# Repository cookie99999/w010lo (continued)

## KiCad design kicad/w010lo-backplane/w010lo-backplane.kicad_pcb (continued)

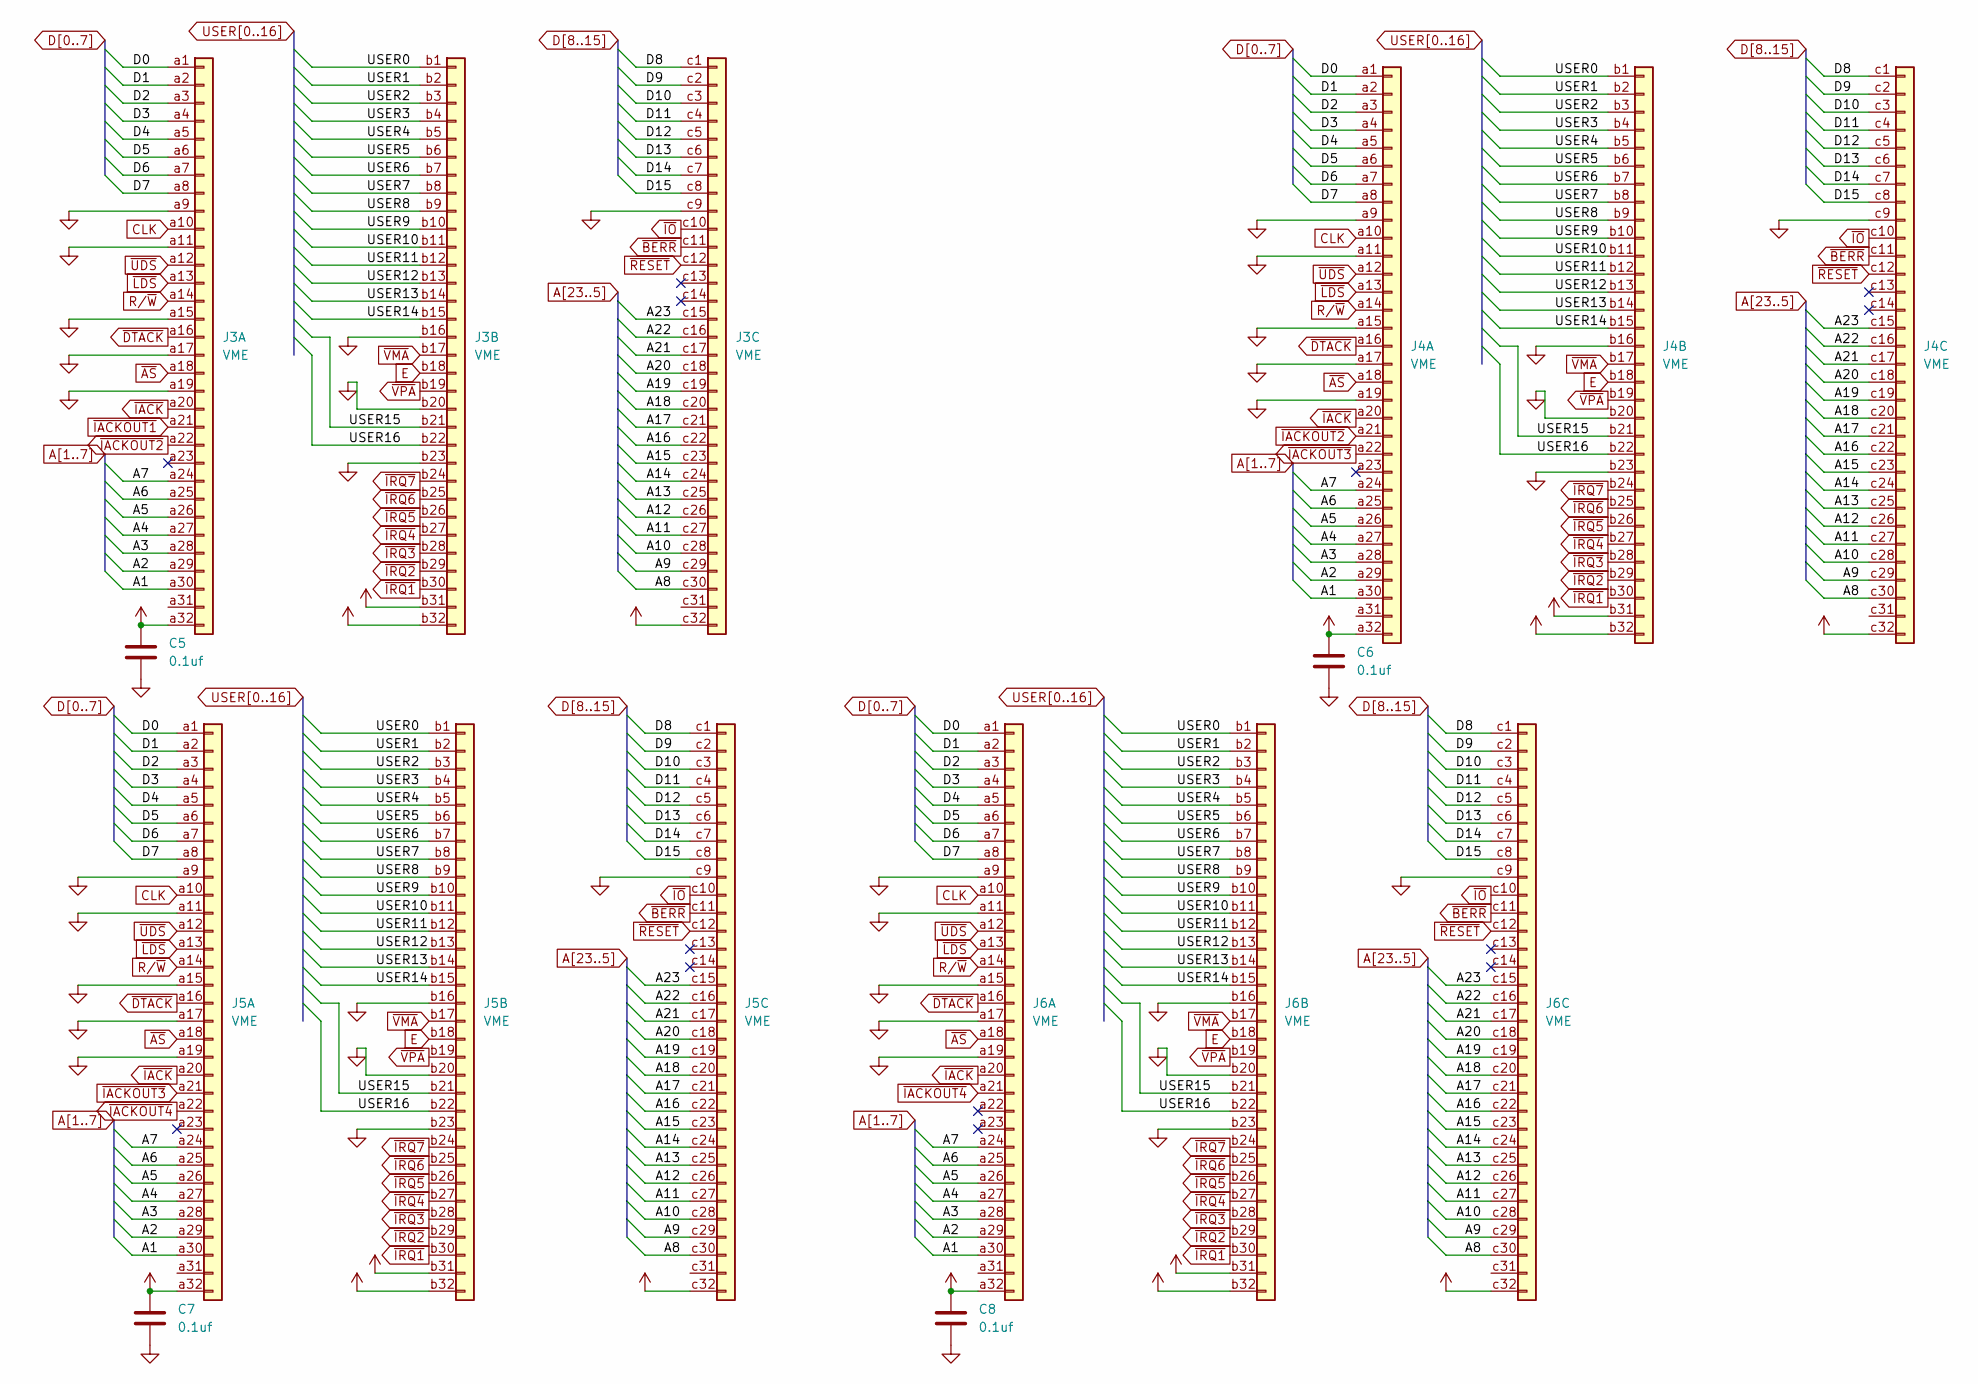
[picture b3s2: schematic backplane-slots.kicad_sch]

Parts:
C5, C6, C7, C8: 0.1uf; C_Disc_D5.0mm_W2.5mm_P5.00mm
J3, J4, J5, J6: VME; DIN41612_C_3x32_Female_Vertical_THT

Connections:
A1: J3.a30, J4.a30, J5.a30, J6.a30; also elsewhere on the board
A2: J3.a29, J4.a29, J5.a29, J6.a29; also elsewhere on the board
A3: J3.a28, J4.a28, J5.a28, J6.a28; also elsewhere on the board
A4: J3.a27, J4.a27, J5.a27, J6.a27; also elsewhere on the board
A5: J3.a26, J4.a26, J5.a26, J6.a26; also elsewhere on the board
A6: J3.a25, J4.a25, J5.a25, J6.a25; also elsewhere on the board
A7: J3.a24, J4.a24, J5.a24, J6.a24; also elsewhere on the board
A8: J3.c30, J4.c30, J5.c30, J6.c30; also elsewhere on the board
A9: J3.c29, J4.c29, J5.c29, J6.c29; also elsewhere on the board
A10: J3.c28, J4.c28, J5.c28, J6.c28; also elsewhere on the board
A11: J3.c27, J4.c27, J5.c27, J6.c27; also elsewhere on the board
A12: J3.c26, J4.c26, J5.c26, J6.c26; also elsewhere on the board
A13: J3.c25, J4.c25, J5.c25, J6.c25; also elsewhere on the board
A14: J3.c24, J4.c24, J5.c24, J6.c24; also elsewhere on the board
A15: J3.c23, J4.c23, J5.c23, J6.c23; also elsewhere on the board
A16: J3.c22, J4.c22, J5.c22, J6.c22; also elsewhere on the board
A17: J3.c21, J4.c21, J5.c21, J6.c21; also elsewhere on the board
A18: J3.c20, J4.c20, J5.c20, J6.c20; also elsewhere on the board
A19: J3.c19, J4.c19, J5.c19, J6.c19; also elsewhere on the board
A20: J3.c18, J4.c18, J5.c18, J6.c18; also elsewhere on the board
A21: J3.c17, J4.c17, J5.c17, J6.c17; also elsewhere on the board
A22: J3.c16, J4.c16, J5.c16, J6.c16; also elsewhere on the board
A23: J3.c15, J4.c15, J5.c15, J6.c15; also elsewhere on the board
CLK: J3.a10, J4.a10, J5.a10, J6.a10; also elsewhere on the board
D0: J3.a1, J4.a1, J5.a1, J6.a1; also elsewhere on the board
D1: J3.a2, J4.a2, J5.a2, J6.a2; also elsewhere on the board
D2: J3.a3, J4.a3, J5.a3, J6.a3; also elsewhere on the board
D3: J3.a4, J4.a4, J5.a4, J6.a4; also elsewhere on the board
D4: J3.a5, J4.a5, J5.a5, J6.a5; also elsewhere on the board
D5: J3.a6, J4.a6, J5.a6, J6.a6; also elsewhere on the board
D6: J3.a7, J4.a7, J5.a7, J6.a7; also elsewhere on the board
D7: J3.a8, J4.a8, J5.a8, J6.a8; also elsewhere on the board
D8: J3.c1, J4.c1, J5.c1, J6.c1; also elsewhere on the board
D9: J3.c2, J4.c2, J5.c2, J6.c2; also elsewhere on the board
D10: J3.c3, J4.c3, J5.c3, J6.c3; also elsewhere on the board
D11: J3.c4, J4.c4, J5.c4, J6.c4; also elsewhere on the board
D12: J3.c5, J4.c5, J5.c5, J6.c5; also elsewhere on the board
D13: J3.c6, J4.c6, J5.c6, J6.c6; also elsewhere on the board
D14: J3.c7, J4.c7, J5.c7, J6.c7; also elsewhere on the board
D15: J3.c8, J4.c8, J5.c8, J6.c8; also elsewhere on the board
E: J3.b18, J4.b18, J5.b18, J6.b18; also elsewhere on the board
GND: C5.2, C6.2, C7.2, C8.2, J3.a9, J3.a11, J3.a15, J3.a17, J3.a19, J3.b16, J3.b20, J3.b23, J3.c9, J4.a9, J4.a11, J4.a15, J4.a17, J4.a19, J4.b16, J4.b20, J4.b23, J4.c9, J5.a9, J5.a11, J5.a15, J5.a17, J5.a19, J5.b16, J5.b20, J5.b23, J5.c9, J6.a9, J6.a11, J6.a15, J6.a17, J6.a19, J6.b16, J6.b20, J6.b23, J6.c9; also elsewhere on the board
R/~W: J3.a14, J4.a14, J5.a14, J6.a14; also elsewhere on the board
USER0: J3.b1, J4.b1, J5.b1, J6.b1; also elsewhere on the board
USER1: J3.b2, J4.b2, J5.b2, J6.b2; also elsewhere on the board
USER2: J3.b3, J4.b3, J5.b3, J6.b3; also elsewhere on the board
USER3: J3.b4, J4.b4, J5.b4, J6.b4; also elsewhere on the board
USER4: J3.b5, J4.b5, J5.b5, J6.b5; also elsewhere on the board
USER5: J3.b6, J4.b6, J5.b6, J6.b6; also elsewhere on the board
USER6: J3.b7, J4.b7, J5.b7, J6.b7; also elsewhere on the board
USER7: J3.b8, J4.b8, J5.b8, J6.b8; also elsewhere on the board
USER8: J3.b9, J4.b9, J5.b9, J6.b9; also elsewhere on the board
USER9: J3.b10, J4.b10, J5.b10, J6.b10; also elsewhere on the board
USER10: J3.b11, J4.b11, J5.b11, J6.b11; also elsewhere on the board
USER11: J3.b12, J4.b12, J5.b12, J6.b12; also elsewhere on the board
USER12: J3.b13, J4.b13, J5.b13, J6.b13; also elsewhere on the board
USER13: J3.b14, J4.b14, J5.b14, J6.b14; also elsewhere on the board
USER14: J3.b15, J4.b15, J5.b15, J6.b15; also elsewhere on the board
USER15: J3.b21, J4.b21, J5.b21, J6.b21; also elsewhere on the board
USER16: J3.b22, J4.b22, J5.b22, J6.b22; also elsewhere on the board
VCC: C5.1, C6.1, C7.1, C8.1, J3.a32, J3.b31, J3.b32, J3.c32, J4.a32, J4.b31, J4.b32, J4.c32, J5.a32, J5.b31, J5.b32, J5.c32, J6.a32, J6.b31, J6.b32, J6.c32; also elsewhere on the board
~AS: J3.a18, J4.a18, J5.a18, J6.a18; also elsewhere on the board
~BERR: J3.c11, J4.c11, J5.c11, J6.c11; also elsewhere on the board
~DTACK: J3.a16, J4.a16, J5.a16, J6.a16; also elsewhere on the board
~IACKOUT1: J3.a21; also elsewhere on the board
~IACKOUT2: J3.a22, J4.a21
~IACKOUT3: J4.a22, J5.a21
~IACKOUT4: J5.a22, J6.a21
~IACK: J3.a20, J4.a20, J5.a20, J6.a20; also elsewhere on the board
~IO: J3.c10, J4.c10, J5.c10, J6.c10; also elsewhere on the board
~IRQ1: J3.b30, J4.b30, J5.b30, J6.b30; also elsewhere on the board
~IRQ2: J3.b29, J4.b29, J5.b29, J6.b29; also elsewhere on the board
~IRQ3: J3.b28, J4.b28, J5.b28, J6.b28; also elsewhere on the board
~IRQ4: J3.b27, J4.b27, J5.b27, J6.b27; also elsewhere on the board
~IRQ5: J3.b26, J4.b26, J5.b26, J6.b26; also elsewhere on the board
~IRQ6: J3.b25, J4.b25, J5.b25, J6.b25; also elsewhere on the board
~IRQ7: J3.b24, J4.b24, J5.b24, J6.b24; also elsewhere on the board
~LDS: J3.a13, J4.a13, J5.a13, J6.a13; also elsewhere on the board
~RESET: J3.c12, J4.c12, J5.c12, J6.c12; also elsewhere on the board
~UDS: J3.a12, J4.a12, J5.a12, J6.a12; also elsewhere on the board
~VMA: J3.b17, J4.b17, J5.b17, J6.b17; also elsewhere on the board
~VPA: J3.b19, J4.b19, J5.b19, J6.b19; also elsewhere on the board

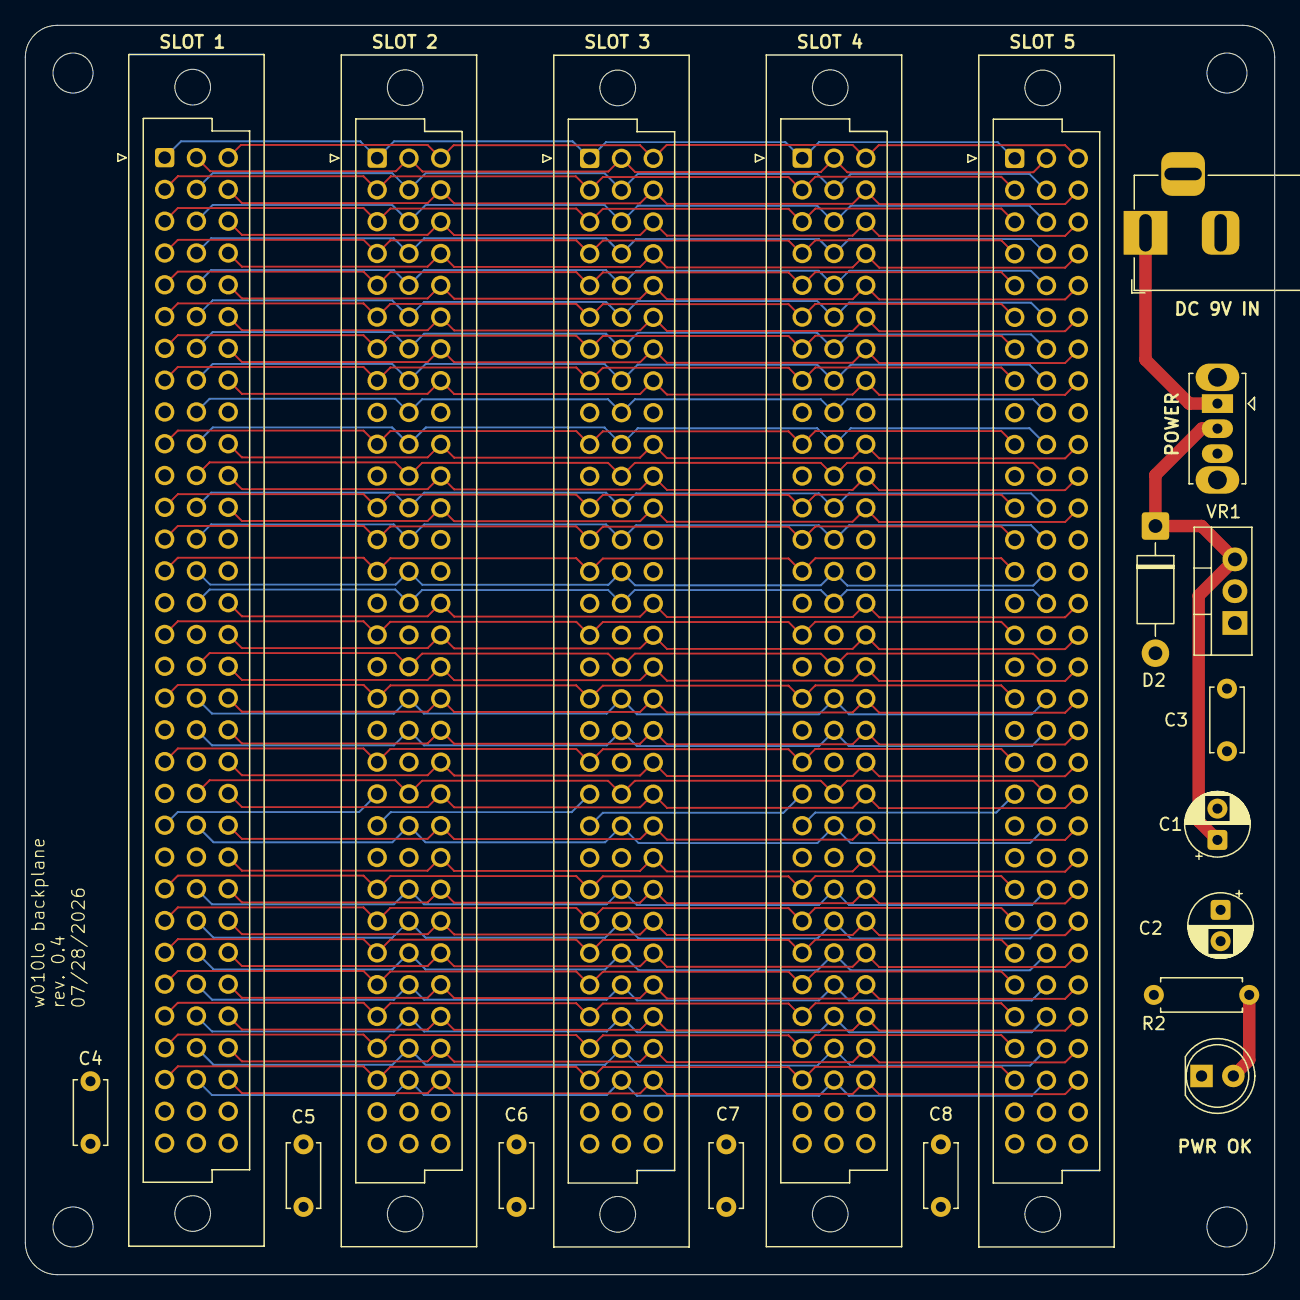
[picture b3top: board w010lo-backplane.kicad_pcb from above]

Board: 4 copper layers, 99.8 x 99.8 mm, 23 parts (0 on the bottom side), 85 nets.

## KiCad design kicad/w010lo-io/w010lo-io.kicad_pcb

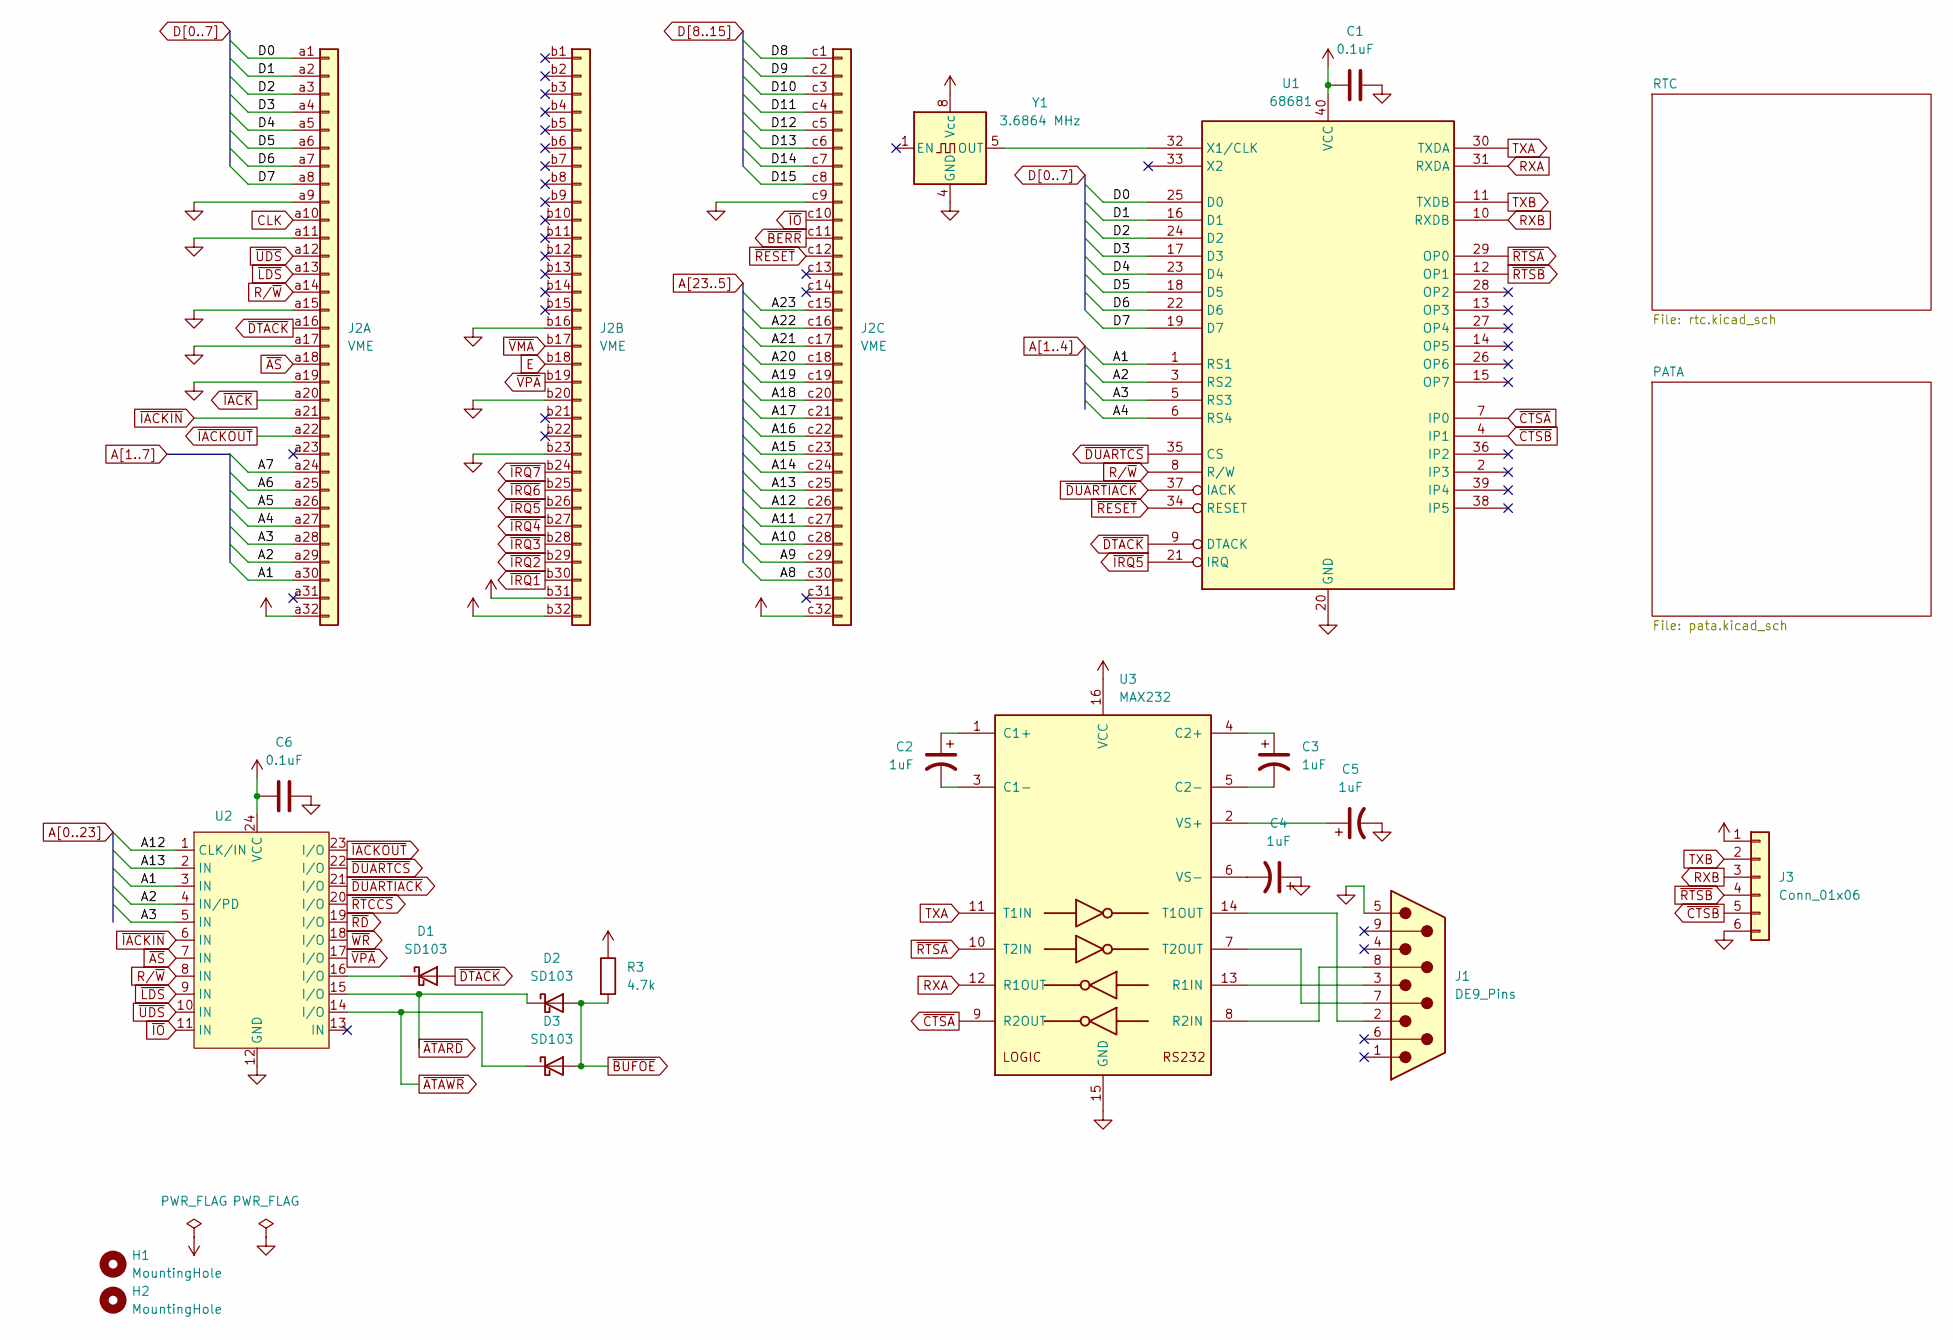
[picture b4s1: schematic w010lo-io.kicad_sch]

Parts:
C1, C6: 0.1uF; C_Disc_D5.0mm_W2.5mm_P5.00mm
C2, C3, C4, C5: 1uF; CP_Radial_D5.0mm_P2.50mm
D1, D2, D3: SD103; D_DO-35_SOD27_P7.62mm_Horizontal
H1, H2: MountingHole; MountingHole_3.2mm_M3
J1: DE9_Pins; DE-9-Amphenol
J2: VME; DIN41612_C_3x32_Male_Horizontal_THT
J3: Conn_01x06; PinHeader_1x06_P2.54mm_Horizontal
R3: 4.7k; R_Axial_DIN0207_L6.3mm_D2.5mm_P7.62mm_Horizontal
U1: 68681; DIP-40_W15.24mm_Socket
U2: DIP-24_W7.62mm_Socket
U3: MAX232; DIP-16_W7.62mm_Socket
Y1: 3.6864 MHz; Oscillator_DIP-8

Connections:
A1: J2.a30, U1.1 (RS1), U2.3 (IN); also elsewhere on the board
A2: J2.a29, U1.3 (RS2), U2.4 (IN/PD); also elsewhere on the board
A3: J2.a28, U1.5 (RS3), U2.5 (IN); also elsewhere on the board
A4: J2.a27, U1.6 (RS4); also elsewhere on the board
A5: J2.a26; also elsewhere on the board
A6: J2.a25; also elsewhere on the board
A7: J2.a24; also elsewhere on the board
A8: J2.c30; also elsewhere on the board
A9: J2.c29; also elsewhere on the board
A10: J2.c28; also elsewhere on the board
A11: J2.c27; also elsewhere on the board
A12: J2.c26, U2.1 (CLK/IN)
A13: J2.c25, U2.2 (IN)
A14: J2.c24
A15: J2.c23
A16: J2.c22
A17: J2.c21
A18: J2.c20
A19: J2.c19
A20: J2.c18
A21: J2.c17
A22: J2.c16
A23: J2.c15
CLK: J2.a10
D0: J2.a1, U1.25 (D0); also elsewhere on the board
D1: J2.a2, U1.16 (D1); also elsewhere on the board
D2: J2.a3, U1.24 (D2); also elsewhere on the board
D3: J2.a4, U1.17 (D3); also elsewhere on the board
D4: J2.a5, U1.23 (D4); also elsewhere on the board
D5: J2.a6, U1.18 (D5); also elsewhere on the board
D6: J2.a7, U1.22 (D6); also elsewhere on the board
D7: J2.a8, U1.19 (D7); also elsewhere on the board
D8: J2.c1; also elsewhere on the board
D9: J2.c2; also elsewhere on the board
D10: J2.c3; also elsewhere on the board
D11: J2.c4; also elsewhere on the board
D12: J2.c5; also elsewhere on the board
D13: J2.c6; also elsewhere on the board
D14: J2.c7; also elsewhere on the board
D15: J2.c8; also elsewhere on the board
E: J2.b18
GND: C1.2, C4.1, C5.2, C6.2, J1.5, J2.a9, J2.a11, J2.a15, J2.a17, J2.a19, J2.b16, J2.b20, J2.b23, J2.c9, J3.6, U1.20 (GND), U2.12 (GND), U3.15 (GND), Y1.4 (GND); also elsewhere on the board
unnamed: D1.1 (K), U2.16 (I/O)
unnamed: U1.32 (X1/CLK), Y1.5 (OUT)
unnamed: C2.1, U3.1 (C1+)
unnamed: C2.2, U3.3 (C1-)
unnamed: C3.1, U3.4 (C2+)
unnamed: C3.2, U3.5 (C2-)
unnamed: J1.3, U3.13 (R1IN)
unnamed: J1.8, U3.8 (R2IN)
unnamed: J1.2, U3.14 (T1OUT)
unnamed: J1.7, U3.7 (T2OUT)
unnamed: C5.1, U3.2 (VS+)
unnamed: C4.2, U3.6 (VS-)
RXA: U1.31 (RXDA), U3.12 (R1OUT)
RXB: J3.3, U1.10 (RXDB)
R/~W: J2.a14, U1.8 (R/W), U2.8 (IN); also elsewhere on the board
TXA: U1.30 (TXDA), U3.11 (T1IN)
TXB: J3.2, U1.11 (TXDB)
VCC: C1.1, C6.1, J2.a32, J2.b31, J2.b32, J2.c32, J3.1, R3.1, U1.40 (VCC), U2.24 (VCC), U3.16 (VCC), Y1.8 (Vcc); also elsewhere on the board
~AS: J2.a18, U2.7 (IN)
~ATARD: D2.1 (K), U2.15 (I/O); also elsewhere on the board
~ATAWR: D3.1 (K), U2.14 (I/O); also elsewhere on the board
~BERR: J2.c11
~BUFOE: D2.2 (A), D3.2 (A), R3.2; also elsewhere on the board
~CTSA: U1.7 (IP0), U3.9 (R2OUT)
~CTSB: J3.5, U1.4 (IP1)
~DTACK: D1.2 (A), J2.a16, U1.9 (DTACK)
~DUARTCS: U1.35 (CS), U2.22 (I/O)
~DUARTIACK: U1.37 (IACK), U2.21 (I/O)
~IACKIN: J2.a21, U2.6 (IN)
~IACKOUT: J2.a22, U2.23 (I/O)
~IACK: J2.a20
~IO: J2.c10, U2.11 (IN)
~IRQ1: J2.b30
~IRQ2: J2.b29
~IRQ3: J2.b28; also elsewhere on the board
~IRQ4: J2.b27
~IRQ5: J2.b26, U1.21 (IRQ)
~IRQ6: J2.b25
~IRQ7: J2.b24
~LDS: J2.a13, U2.9 (IN)
~RD: U2.19 (I/O); also elsewhere on the board
~RESET: J2.c12, U1.34 (RESET); also elsewhere on the board
~RTCCS: U2.20 (I/O); also elsewhere on the board
~RTSA: U1.29 (OP0), U3.10 (T2IN)
~RTSB: J3.4, U1.12 (OP1)
~UDS: J2.a12, U2.10 (IN)
~VMA: J2.b17
~VPA: J2.b19, U2.17 (I/O)
~WR: U2.18 (I/O); also elsewhere on the board

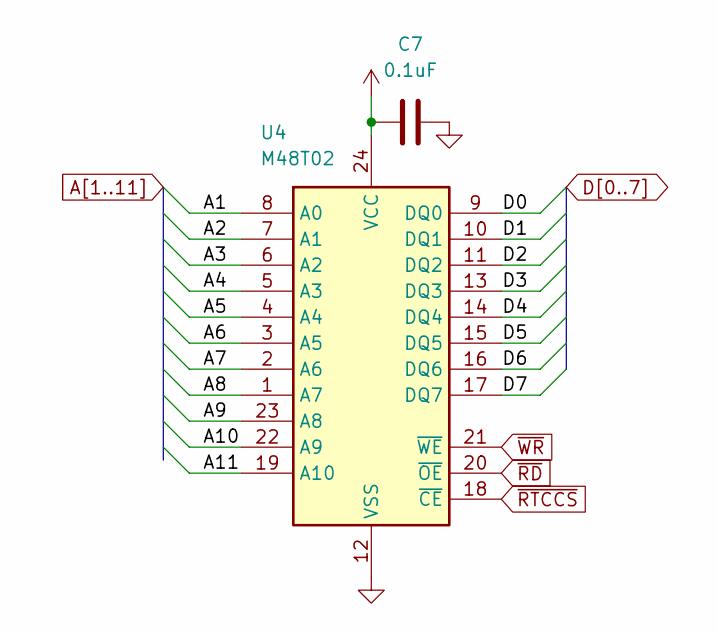
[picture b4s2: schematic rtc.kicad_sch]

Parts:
C7: 0.1uF; C_Disc_D5.0mm_W2.5mm_P5.00mm
U4: M48T02; DIP1562W53P279L3454H965Q24N; Mouser Part Number 511-M48T0270PC1

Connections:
A1: U4.8 (A0); also elsewhere on the board
A2: U4.7 (A1); also elsewhere on the board
A3: U4.6 (A2); also elsewhere on the board
A4: U4.5 (A3); also elsewhere on the board
A5: U4.4 (A4); also elsewhere on the board
A6: U4.3 (A5); also elsewhere on the board
A7: U4.2 (A6); also elsewhere on the board
A8: U4.1 (A7); also elsewhere on the board
A9: U4.23 (A8); also elsewhere on the board
A10: U4.22 (A9); also elsewhere on the board
A11: U4.19 (A10); also elsewhere on the board
D0: U4.9 (DQ0); also elsewhere on the board
D1: U4.10 (DQ1); also elsewhere on the board
D2: U4.11 (DQ2); also elsewhere on the board
D3: U4.13 (DQ3); also elsewhere on the board
D4: U4.14 (DQ4); also elsewhere on the board
D5: U4.15 (DQ5); also elsewhere on the board
D6: U4.16 (DQ6); also elsewhere on the board
D7: U4.17 (DQ7); also elsewhere on the board
GND: C7.2, U4.12 (VSS); also elsewhere on the board
VCC: C7.1, U4.24 (VCC); also elsewhere on the board
~RD: U4.20 (~OE); also elsewhere on the board
~RTCCS: U4.18 (~CE); also elsewhere on the board
~WR: U4.21 (~WE); also elsewhere on the board

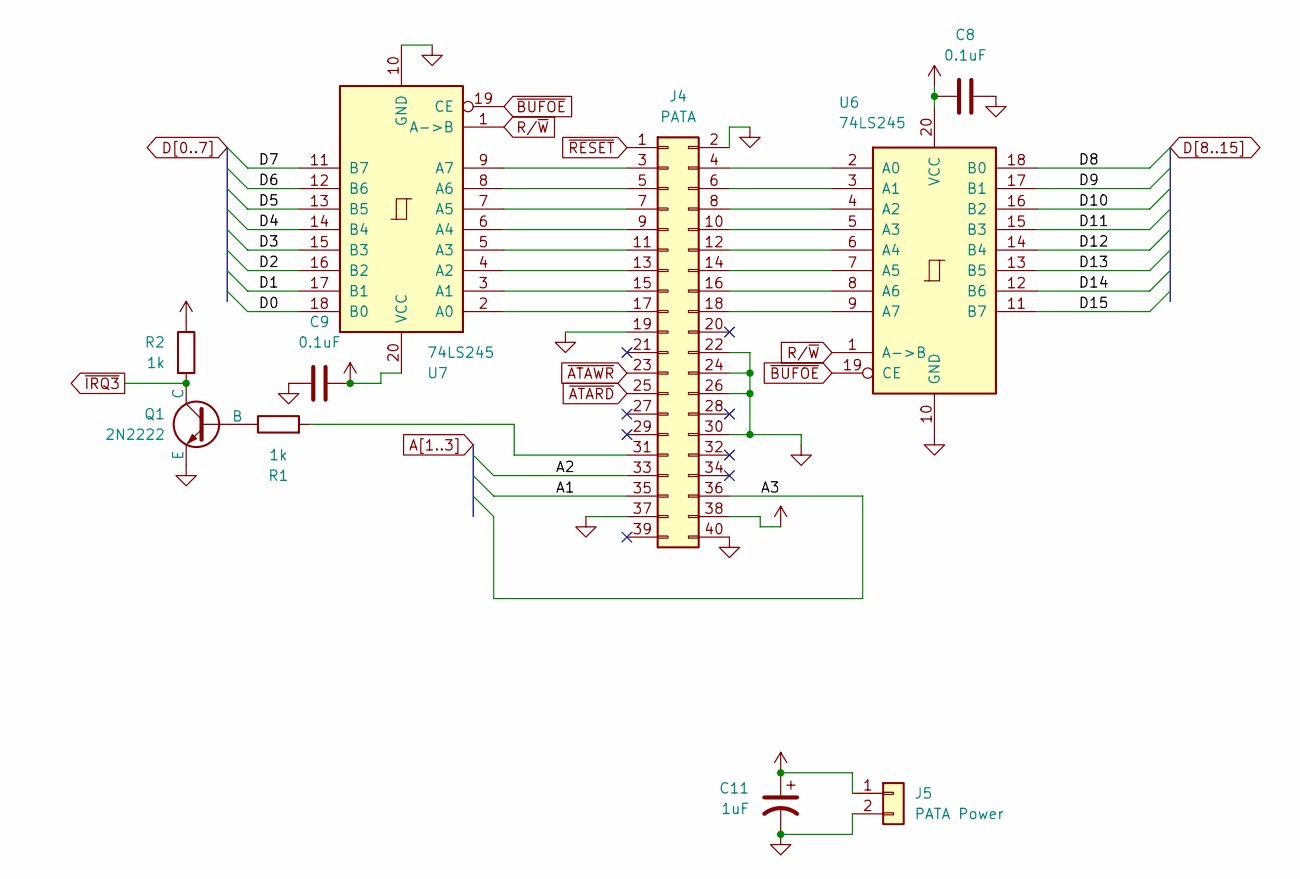
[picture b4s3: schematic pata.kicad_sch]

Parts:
C8, C9: 0.1uF; C_Disc_D5.0mm_W2.5mm_P5.00mm
C11: 1uF; CP_Radial_D5.0mm_P2.50mm
J4: PATA; IDC-Header_2x20_P2.54mm_Horizontal
J5: PATA Power; PinHeader_1x02_P2.54mm_Horizontal
Q1: 2N2222; TO-92
R1, R2: 1k; R_Axial_DIN0207_L6.3mm_D2.5mm_P7.62mm_Horizontal
U6, U7: 74LS245; DIP-20_W7.62mm_Socket

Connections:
A1: J4.35; also elsewhere on the board
A2: J4.33; also elsewhere on the board
A3: J4.36; also elsewhere on the board
D0: U7.18 (B0); also elsewhere on the board
D1: U7.17 (B1); also elsewhere on the board
D2: U7.16 (B2); also elsewhere on the board
D3: U7.15 (B3); also elsewhere on the board
D4: U7.14 (B4); also elsewhere on the board
D5: U7.13 (B5); also elsewhere on the board
D6: U7.12 (B6); also elsewhere on the board
D7: U7.11 (B7); also elsewhere on the board
D8: U6.18 (B0); also elsewhere on the board
D9: U6.17 (B1); also elsewhere on the board
D10: U6.16 (B2); also elsewhere on the board
D11: U6.15 (B3); also elsewhere on the board
D12: U6.14 (B4); also elsewhere on the board
D13: U6.13 (B5); also elsewhere on the board
D14: U6.12 (B6); also elsewhere on the board
D15: U6.11 (B7); also elsewhere on the board
GND: C8.2, C9.2, C11.2, J4.2, J4.19, J4.22, J4.24, J4.26, J4.30, J4.37, J4.40, J5.2, Q1.3 (E), U6.10 (GND), U7.10 (GND); also elsewhere on the board
unnamed: J4.3, U7.9 (A7)
unnamed: J4.4, U6.2 (A0)
unnamed: J4.5, U7.8 (A6)
unnamed: J4.6, U6.3 (A1)
unnamed: J4.7, U7.7 (A5)
unnamed: J4.8, U6.4 (A2)
unnamed: J4.9, U7.6 (A4)
unnamed: J4.10, U6.5 (A3)
unnamed: J4.11, U7.5 (A3)
unnamed: J4.12, U6.6 (A4)
unnamed: J4.13, U7.4 (A2)
unnamed: J4.14, U6.7 (A5)
unnamed: J4.15, U7.3 (A1)
unnamed: J4.16, U6.8 (A6)
unnamed: J4.17, U7.2 (A0)
unnamed: J4.18, U6.9 (A7)
unnamed: J4.31, R1.2
unnamed: Q1.2 (B), R1.1
R/~W: U6.1 (A->B), U7.1 (A->B); also elsewhere on the board
VCC: C8.1, C9.1, C11.1, J4.38, J5.1, R2.1, U6.20 (VCC), U7.20 (VCC); also elsewhere on the board
~ATARD: J4.25; also elsewhere on the board
~ATAWR: J4.23; also elsewhere on the board
~BUFOE: U6.19 (CE), U7.19 (CE); also elsewhere on the board
~IRQ3: Q1.1 (C), R2.2; also elsewhere on the board
~RESET: J4.1; also elsewhere on the board

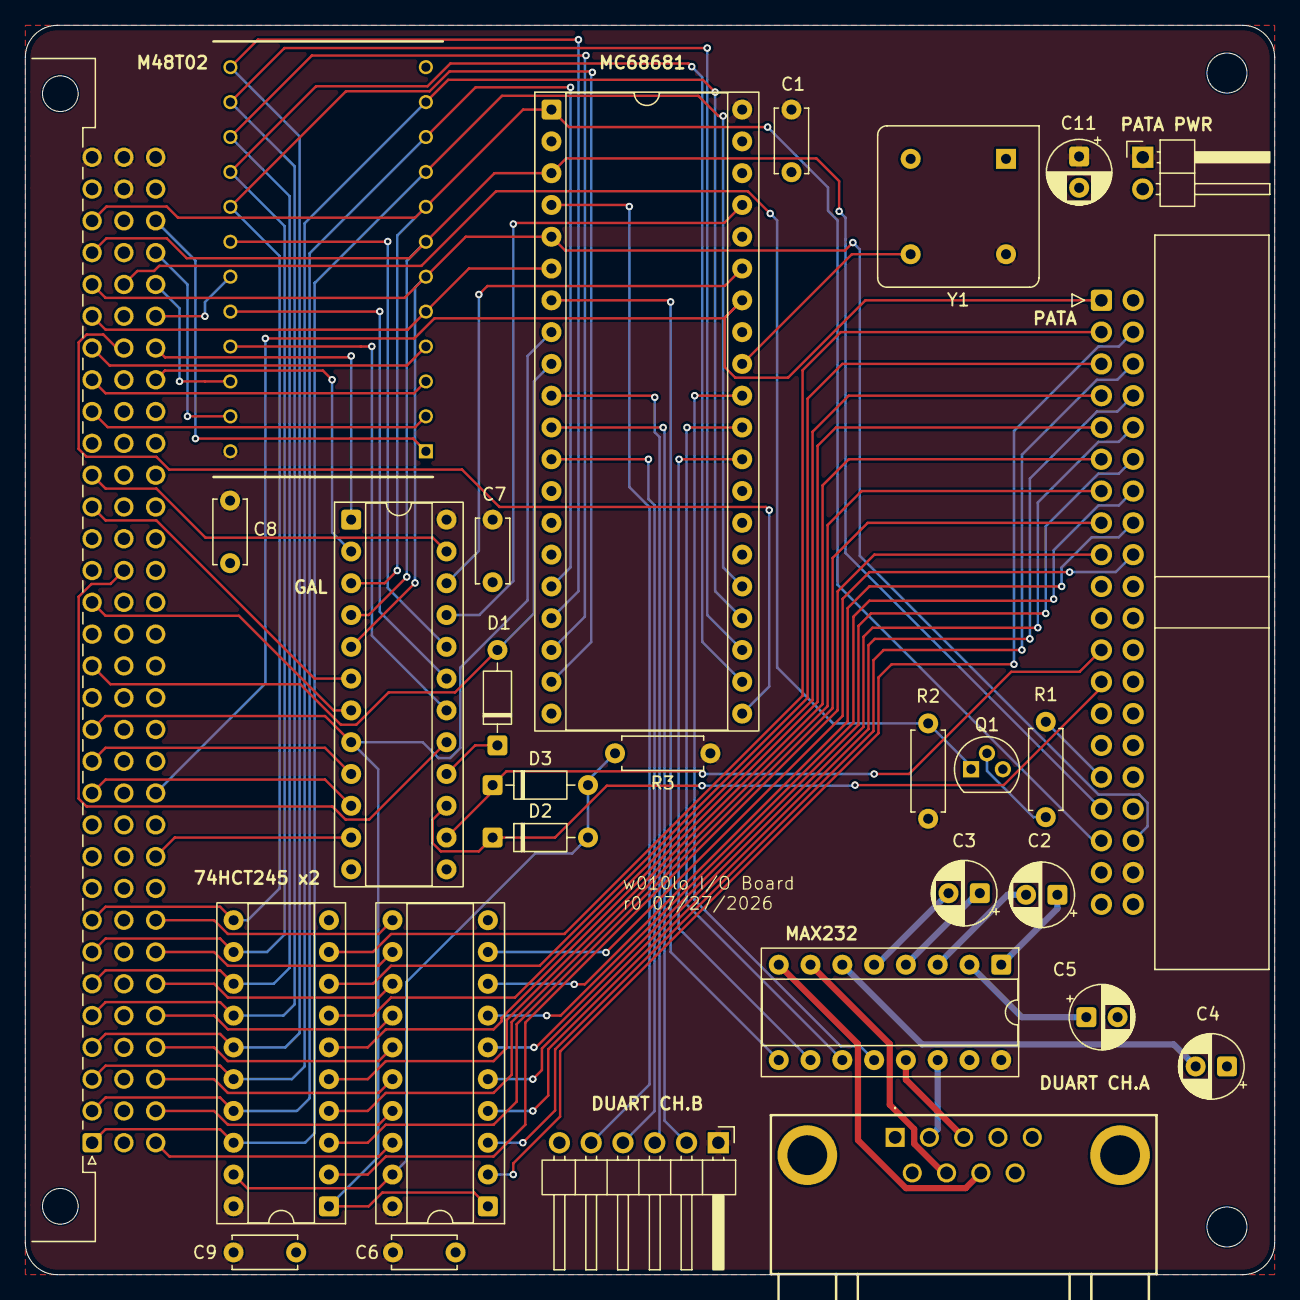
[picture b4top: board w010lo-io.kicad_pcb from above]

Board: 4 copper layers, 99.8 x 99.8 mm, 31 parts (0 on the bottom side), 89 nets.

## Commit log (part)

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2026-05-05 Add schematic
